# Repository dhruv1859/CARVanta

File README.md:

<h1 align="center">🧬 CARVanta</h1>
<h3 align="center">AI-Augmented CAR-T Cell Target Viability Assessment Platform<br>+ Sentinel HYDRA Bedside Biosensor</h3>

<p align="center">
  <strong>117,000+ lines of code • 778 source files • 214 Python modules • 45 React pages • 50 firmware files • 6-layer medical PCB</strong>
</p>

---

## 🎯 What is CARVanta?

**CARVanta** is a closed-loop immunotherapy intelligence system — an **AI software platform** connected to a **bedside biosensor device** — that turns CAR-T cell therapy target selection from art into science.

> **The core problem:** Selecting the right antigen target is the most critical decision in CAR-T therapy design. A wrong target leads to years of wasted R&D and patient harm. CARVanta automates this decision with data-driven scoring validated against FDA-approved targets, and monitors treatment in real time to catch antigen escape before it kills.

### Key Capabilities

| Module | Description |
|--------|-------------|
| 🔬 **CVS Scoring Engine** | 8-feature adaptive weighted algorithm with multi-source consensus |
| 🤖 **ML Ensemble** | Random Forest + XGBoost classifier + regression ranker |
| 🧠 **LLM Integration** | Grok/Groq/Gemini/OpenAI for dynamic clinical reasoning |
| 🧬 **Genomic Profiler** | Variant calling, HLA typing, TMB calculation, neoantigen prediction |
| 🧑‍⚕️ **Digital Twin** | Patient-specific CRS/ICANS simulation with pharmacokinetic modeling |
| 📊 **Clinical Trials** | Safety monitoring, DSMB reports, RWE analysis, regulatory intelligence |
| 🔍 **NLP Search** | Natural language antigen discovery with semantic intent detection |
| 🏆 **Model Validation** | 5-fold CV, FDA ground-truth validation, ISO/IEC 25010 certification |
| 🌐 **Neural Bridge** | 3D knowledge graph visualization of antigen-disease relationships |
| 💊 **Drug Discovery** | scFv designer, toxicity prediction, CAR construct architecture |
| 📈 **Deep Learning** | Autoencoder anomaly detection, attention mechanisms, neural scoring |
| 🔬 **Sentinel HYDRA** | Real-time 4-channel antigen monitoring with bedside biosensor hardware |

---

## 🏗️ Architecture

```
Patient blood (fingerprick)
        │
        ▼
┌───────────────────────┐
│   SENTINEL HYDRA      │     Bedside device — 100×100mm, ~$79/unit
│   RP2040 + ESP32-S3   │     6-layer medical PCB, ENIG finish
│                       │
│   • 4× potentiostat   │     Sensor data
│   • SpO2 + heart rate │     ─────────────────►
│   • 11-ch spectral    │          WiFi (TLS)
│   • Impedance + temp  │
└───────────┬───────────┘
            │
            ▼
┌─────────────────────────────────────────────────────────────┐
│                    CARVANTA CLOUD PLATFORM                    │
├─────────────────────────────────────────────────────────────┤
│                    Frontend (React + Vite)                    │
│  45 pages • Clinical Precision UI • Glassmorphism Design     │
├─────────────────────────────────────────────────────────────┤
│                    FastAPI Backend (v5)                       │
│  28 routers • Async • CORS • Rate limiting • Audit logging   │
├──────────┬──────────┬──────────┬──────────┬─────────────────┤
│ Scoring  │    ML    │   LLM    │ Genomics │   Validation    │
│ Engine   │ Ensemble │ Insight  │ Pipeline │   & Certify     │
│ (CVS v3) │ (RF+XGB) │(Grok/AI) │(VCF/HLA)│  (ISO 25010)   │
├──────────┴──────────┴──────────┴──────────┴─────────────────┤
│              Data Layer (SQLite / PostgreSQL)                 │
│        biomarker_database.csv • 500+ scored antigens         │
└─────────────────────────────────────────────────────────────┘
            │
            ▼
  Doctor's phone: "CD19 dropping — antigen escape risk. Switch to CD22."
```

> For a deep dive into the full system architecture, see [ARCHITECTURE.md](ARCHITECTURE.md).

---

## 🔬 Sentinel HYDRA — Bedside Biosensor

The **Sentinel HYDRA** is a credit-card-sized medical-grade device that continuously monitors blood biomarkers through a disposable sensor strip. It detects antigen escape — the #1 reason CAR-T fails — in **30 seconds** instead of days via lab tests.

### Hardware Specifications

| Parameter | Value |
|-----------|-------|
| Dimensions | 100mm × 100mm |
| PCB Layers | **6** (signal/ground/analog/power/high-speed/bottom) |
| MCUs | **ESP32-S3** (main) + **RP2040** (sensor coprocessor) |
| Antigen Channels | **4 simultaneous** (CD19, CD22, BCMA, GPRC5D) |
| ADC | ADS1256 — **24-bit**, 8-channel, 30kSPS |
| Potentiostat | 4× LMP91000 (one per antigen channel) |
| SpO2/Heart Rate | MAX30102 integrated sensor |
| Spectral | AS7341 — **11 wavelength channels** |
| Temperature | TMP117 (±0.1°C) + MLX90614 (contactless IR) |
| IMU | LSM6DSO — 6-axis (fall detection) |
| Display | 2.4" IPS TFT (320×240, ST7789) |
| Connectivity | WiFi + BLE (ESP32-S3) |
| Data Logging | microSD + DS3231 RTC |
| Power | USB-C + LiPo battery (BQ24075 charger) |
| Surface Finish | ENIG (immersion gold) — biocompatible |
| Cost per Unit | **~$79** (complete with battery + display + sensor) |

### Manufacturing Files

Production-ready Gerber files for PCB fabrication are available:

📦 **[Sentinel_HYDRA_Gerbers.zip](hardware/sentinel/kicad/Sentinel_HYDRA/Sentinel_HYDRA_Gerbers.zip)** — Upload directly to JLCPCB / PCBWay

Contains:
- 6 copper layers (Digital_Signals, GND_Plane, Analog_Signals, Power_Planes, HighSpeed, Bottom_GND)
- Front/Back solder mask, silkscreen, paste stencil
- Board outline (Edge.Cuts)
- Excellon drill files (PTH + NPTH separated)
- Drill map files
- Gerber job file

> For the full Bill of Materials, see [BOM.md](hardware/sentinel/BOM.md).

---

## 🚀 Quick Start

### Prerequisites

- Python 3.12+
- Node.js 18+
- Git

### 1. Clone & Setup

```bash
git clone https://github.com/dhruv1859/CARVanta.git
cd CARVanta

# Backend
pip install -r requirements.txt
copy .env.example .env
# Edit .env — add your XAI_API_KEY or GROQ_API_KEY for LLM features

# Frontend
cd frontend-react
npm install
```

### 2. Run Locally

```bash
# Terminal 1 — Backend
py -m uvicorn api.main:app --host 0.0.0.0 --port 8001

# Terminal 2 — Frontend
cd frontend-react
npm run dev
```

Open **http://localhost:5173** → full platform is live.

### 3. Train ML Models (Optional)

```bash
py models/train_pipeline.py
```

This runs 5-fold stratified cross-validation and trains the RF+XGBoost ensemble + regression ranker.

### 4. Build Firmware (Optional)

Requires [PlatformIO](https://platformio.org/install):

```bash
# ESP32 main controller
cd hardware/sentinel/firmware/esp32_hydra
pio run

# RP2040 sensor coprocessor
cd hardware/sentinel/firmware/rp2040_hydra
pio run
```

---

## 🧪 Scoring Algorithm

### CVS (CAR-T Viability Score) v3

CARVanta's **original** 8-feature Adaptive Weighted Scoring:

| Feature | Weight | Source |
|---------|--------|--------|
| Tumor Specificity | 25% | TCGA differential expression |
| Safety Score | 20% | GTEx normal tissue risk (inverted) |
| Stability | 12% | Expression consistency |
| Evidence | 10% | Published clinical support |
| Immunogenicity | 10% | Immune recognition potential |
| Surface Accessibility | 8% | UniProt/HPA membrane localization |
| Tissue Risk | 8% | GTEx organ-level heatmap |
| Protein Validation | 7% | HPA protein-level confirmation |

**Adaptive Weight Adjustment:** When real data sources (TCGA, GTEx, HPA) are available, feature weights dynamically shift to give more credence to features backed by real data vs. estimated values.

### ML Ensemble (v4)

The final score blends rule-based CVS with ML predictions:

```
Adaptive Score = (1 - α) × CVS + α × ML_score
```

Where `α` is dynamically adjusted based on data confidence (range: 0.20–0.40).

---

## 🏆 Model Validation & Certification

CARVanta includes a **production-grade validation suite** aligned with ISO/IEC 25010:

| Test | Method | What It Proves |
|------|--------|----------------|
| **Classifier CV** | 5-fold Stratified K-Fold | Accuracy, F1, AUC-ROC, Precision, Recall |
| **Ranker CV** | 5-fold K-Fold Regression | R², MAE, RMSE, Spearman ρ |
| **FDA Ground-Truth** | CD19, BCMA, CD22, GPRC5D | All approved targets must score Tier 1 |
| **Negative Controls** | TP53, RB1, BRCA1, PTEN, APC | Non-viable targets rejected correctly |
| **Robustness** | ±5% feature perturbation | Measures prediction stability |
| **Statistical Significance** | Paired t-test + Wilcoxon | Model vs. 3 random baselines (p < 0.01) |
| **Calibration** | Brier score + log loss | Probability reliability |

Run validation: `GET /api/v5/validation/run`

---

## 🤖 LLM Integration

CARVanta uses LLMs to generate **dynamic clinical reasoning** instead of hardcoded insights:

- **Supported Providers:** Grok (xAI) → Groq → DeepSeek → Gemini → OpenAI
- **Fallback:** If no LLM key is configured, rule-based insights are served
- **Provenance:** Every AI insight displays a badge showing `🤖 LLM Generated` or `📐 Rule-Based`

Set one key in `.env`:
```
XAI_API_KEY=your-grok-key
# or
GROQ_API_KEY=your-groq-key
```

---

## ☁️ Deploy to Railway

### One-Click Deploy

1. Go to [railway.app](https://railway.app) → **New Project** → **Deploy from GitHub repo**
2. Select `dhruv1859/CARVanta`
3. Railway auto-detects `nixpacks.toml` and builds
4. Add environment variables in Railway dashboard:

| Variable | Required | Description |
|----------|----------|-------------|
| `XAI_API_KEY` | ✅ | Grok API key for LLM insights |
| `CARVANTA_ENV` | Optional | Set to `production` |
| `DATABASE_URL` | Optional | PostgreSQL URL (defaults to SQLite) |

5. Railway assigns a public URL → your API is live

### Frontend Deployment

Deploy the React frontend separately on **Vercel** or **Netlify**:

```bash
cd frontend-react
npm run build
# Upload dist/ to Vercel/Netlify
# Set VITE_API_URL to your Railway backend URL
```

---

## 📁 Project Structure

```
CARVanta/
├── api/                        # 28 FastAPI routers (v5)
│   ├── main.py                 # App entrypoint
│   ├── auth.py                 # JWT authentication
│   ├── validation_router.py    # Model validation endpoints
│   └── ...
├── scoring/                    # CVS scoring engine (v3)
├── models/                     # ML pipeline (RF + XGBoost)
├── features/                   # Feature engineering + LLM + FHIR
├── validation/                 # Model validation & certification
├── deep_learning/              # Autoencoder, attention, neural models
├── genomics/                   # Variant calling, HLA, TMB
├── digital_twin/               # Patient simulation engine
├── discovery/                  # Drug discovery, scFv design
├── copilot/                    # Research assistant, RAG engine
├── trials/                     # Clinical trial intelligence
├── frontend-react/             # React 18 + Vite + TypeScript
│   └── src/pages/              # 45 page modules
├── hardware/
│   └── sentinel/
│       ├── kicad/
│       │   └── Sentinel_HYDRA/         # 6-layer KiCad PCB project
│       │       ├── *.kicad_sch         # 7 schematic sheets
│       │       ├── Sentinel_HYDRA.kicad_pcb
│       │       ├── gerbers/            # Production Gerber files
│       │       └── Sentinel_HYDRA_Gerbers.zip
│       ├── firmware/
│       │   ├── esp32_hydra/            # ESP32-S3 firmware (50 files)
│       │   └── rp2040_hydra/           # RP2040 firmware
│       ├── BOM.md                      # Bill of materials (~$79/unit)
│       └── README.md                   # Hardware documentation
├── data/                       # Biomarker database + reports
├── ARCHITECTURE.md             # Full system architecture
├── nixpacks.toml               # Railway deployment config
├── railway.json                # Railway service config
└── requirements.txt            # Python dependencies
```

---

## 🔑 API Endpoints

### Core Scoring
| Endpoint | Method | Description |
|----------|--------|-------------|
| `/api/v5/score` | POST | Score a single antigen |
| `/api/v5/batch_score` | POST | Score multiple antigens |
| `/api/v5/rankings` | GET | Global antigen leaderboard |
| `/api/v5/nlp/query` | POST | Natural language search |

### Validation
| Endpoint | Method | Description |
|----------|--------|-------------|
| `/api/v5/validation/run` | GET | Full validation suite |
| `/api/v5/validation/quick` | GET | Quick classifier + FDA check |
| `/api/v5/validation/fda-targets` | GET | FDA ground-truth only |
| `/api/v5/validation/certification` | GET | ISO/IEC 25010 report |

### Clinical
| Endpoint | Method | Description |
|----------|--------|-------------|
| `/api/v5/digital-twin/simulate` | POST | Patient simulation |
| `/api/v5/trials/clinical-trials` | GET | Trial lookup by antigen |
| `/api/v5/genomics/analyze-variants` | POST | Genomic variant analysis |

Full API docs: `http://localhost:8001/docs` (Swagger UI)

---

## 🛡️ Security & Compliance

- **ISO/IEC 25010** aligned model validation and certification
- **FDA 21 CFR Part 11** concepts for electronic records
- **GAMP 5** risk-based approach compliance framework
- **LLM Provenance** — all AI outputs labeled with origin (LLM vs Rule-Based)
- **Audit Logging** — all scoring requests logged with timestamps
- **CORS + Rate Limiting** middleware (configurable)

See [security.md](security.md) for vulnerability reporting and [PRIVACY_POLICY.md](PRIVACY_POLICY.md) for HIPAA alignment.

---

## 📄 Documentation

| Document | Description |
|----------|-------------|
| [ARCHITECTURE.md](ARCHITECTURE.md) | Full system architecture (software + hardware + firmware) |
| [BOM.md](hardware/sentinel/BOM.md) | Sentinel HYDRA bill of materials |
| [ROADMAP.md](ROADMAP.md) | Product roadmap and future plans |
| [MODULES.md](MODULES.md) | Module registry and build order |
| [CHANGELOG.md](CHANGELOG.md) | Version history |
| [contributing.md](contributing.md) | Contribution guidelines |
| [security.md](security.md) | Security policy |
| [CODE_OF_CONDUCT.md](CODE_OF_CONDUCT.md) | Community code of conduct |
| [MODEL_CARD.md](MODEL_CARD.md) | ML model documentation |
| [ISO_13485_ALIGNMENT.md](ISO_13485_ALIGNMENT.md) | Quality management alignment |
| [PRIVACY_POLICY.md](PRIVACY_POLICY.md) | HIPAA compliance disclosure |

---

## 📄 License

Business Source License 1.1 (BUSL-1.1). See [LICENSE](LICENSE) for details.

---

## 👨‍💻 Author

**Dhruv** — [@dhruv1859](https://github.com/dhruv1859)

---

<p align="center">
  <strong>CARVanta</strong> — Turning immunotherapy target selection from art into science.
</p>

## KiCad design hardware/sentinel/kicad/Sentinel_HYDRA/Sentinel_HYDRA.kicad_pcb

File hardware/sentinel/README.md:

# CARVanta Sentinel v2.0 — 6-Layer Medical-Grade PCB
## Multi-Channel Antigen Escape Detection System

### Why 6 Layers?

This board monitors **4 antigens simultaneously** (CD19, CD22, BCMA, GPRC5D),
meaning 4 independent electrochemical channels that MUST be electrically isolated
from each other and from the digital noise of the ESP32 + WiFi radio.

A 2-layer board cannot achieve this. Here's why each layer exists:

```
Layer 1 (F.Cu)  — Digital signals: SPI, I2C, UART, USB, GPIO
Layer 2 (GND)   — Continuous ground plane (EMI shield between digital & analog)
Layer 3 (INNER1)— Analog signals: 4× potentiostat outputs, ADC inputs, sensor traces
Layer 4 (PWR)   — Power planes: 3.3V_DIGITAL, 3.3V_ANALOG, 1.8V_CORE, VBAT
Layer 5 (INNER2)— High-speed: USB 2.0 differential pair, WiFi RF routing
Layer 6 (B.Cu)  — Component pads, ground pour, thermal relief
```

### Board Specifications

| Parameter | v1.0 (old) | v2.0 (new) |
|-----------|-----------|-----------|
| Dimensions | 80×55mm | 95×65mm |
| Layers | 2 | **6** |
| Channels | 1 antigen | **4 simultaneous** |
| ADC | 1× ADS1115 (16-bit) | **1× ADS1256 (24-bit, 8ch)** |
| Potentiostat | 1× LMP91000 | **4× LMP91000** |
| Power domains | 1 (3.3V) | **4 (3.3V_D, 3.3V_A, 1.8V, VBAT)** |
| Analog isolation | None | **Split ground plane + ferrite bead** |
| Data logging | None | **microSD + RTC** |
| Patient vitals | None | **MAX30102 SpO2/HR + MLX90614 temp** |
| Impedance control | No | **90Ω USB, 50Ω RF** |
| ESD protection | No | **TVS diodes on all I/O** |
| Cost per unit | $17 | **~$45-55** |

### Stackup (6-Layer, 1.6mm FR4)

```
┌─────────────────────────────────────────────────────────┐
│ Layer 1: F.Cu (Signal - Digital)          35µm copper   │
│   └─ SPI bus, I2C bus, UART, GPIO, LED data            │
├─────────────────────────────────────────────────────────┤
│ Prepreg: 0.2mm FR4 (εr=4.5)                            │
├─────────────────────────────────────────────────────────┤
│ Layer 2: GND (Solid Ground Plane)         35µm copper   │
│   └─ Continuous pour, NO cuts, NO traces                │
│   └─ Acts as EMI shield between digital L1 & analog L3 │
├─────────────────────────────────────────────────────────┤
│ Core: 0.36mm FR4                                        │
├─────────────────────────────────────────────────────────┤
│ Layer 3: INNER1 (Signal - Analog)         35µm copper   │
│   └─ 4× LMP91000 VOUT traces (guarded)                 │
│   └─ ADS1256 analog inputs (star routing)               │
│   └─ Sensor connector traces (kelvin connection)        │
├─────────────────────────────────────────────────────────┤
│ Prepreg: 0.2mm FR4                                      │
├─────────────────────────────────────────────────────────┤
│ Layer 4: PWR (Power Planes)               35µm copper   │
│   └─ Zone 1: 3.3V_DIGITAL (ESP32, TFT, LEDs)          │
│   └─ Zone 2: 3.3V_ANALOG (LMP91000s, ADS1256)         │
│   └─ Zone 3: VBAT (battery direct)                      │
│   └─ Zone 4: 1.8V (ESP32 core, if needed)              │
├─────────────────────────────────────────────────────────┤
│ Core: 0.36mm FR4                                        │
├─────────────────────────────────────────────────────────┤
│ Layer 5: INNER2 (High-Speed Signals)      35µm copper   │
│   └─ USB D+/D- differential pair (90Ω impedance)       │
│   └─ ESP32 antenna feed (50Ω microstrip)                │
│   └─ SD card high-speed data lines                      │
├─────────────────────────────────────────────────────────┤
│ Prepreg: 0.2mm FR4                                      │
├─────────────────────────────────────────────────────────┤
│ Layer 6: B.Cu (Signal + Ground Pour)      35µm copper   │
│   └─ Component pads (bottom-side ICs)                   │
│   └─ Ground pour for thermal dissipation                │
│   └─ Mounting hole connections                          │
└─────────────────────────────────────────────────────────┘
Total thickness: ~1.6mm
```

### Design Rules (Medical Grade)

| Rule | Value | Reason |
|------|-------|--------|
| Min trace width | 0.15mm (6mil) | JLCPCB 6-layer capability |
| Min clearance | 0.15mm | IPC-2221 Class 2 |
| USB diff pair | 0.18mm trace, 0.15mm gap | 90Ω impedance on L5 |
| Analog traces | 0.25mm, guarded | Noise rejection |
| Power traces | 0.5mm minimum | Current handling |
| Via size | 0.3mm drill, 0.6mm pad | Standard via |
| Via-in-pad | Allowed (filled & capped) | For QFN packages |
| Copper weight | 1oz (35µm) all layers | Standard |
| Surface finish | ENIG (gold) | Corrosion resistance, biocompat |
| Solder mask | Matte black | Premium aesthetic |
| Silkscreen | White, both sides | Component labels |

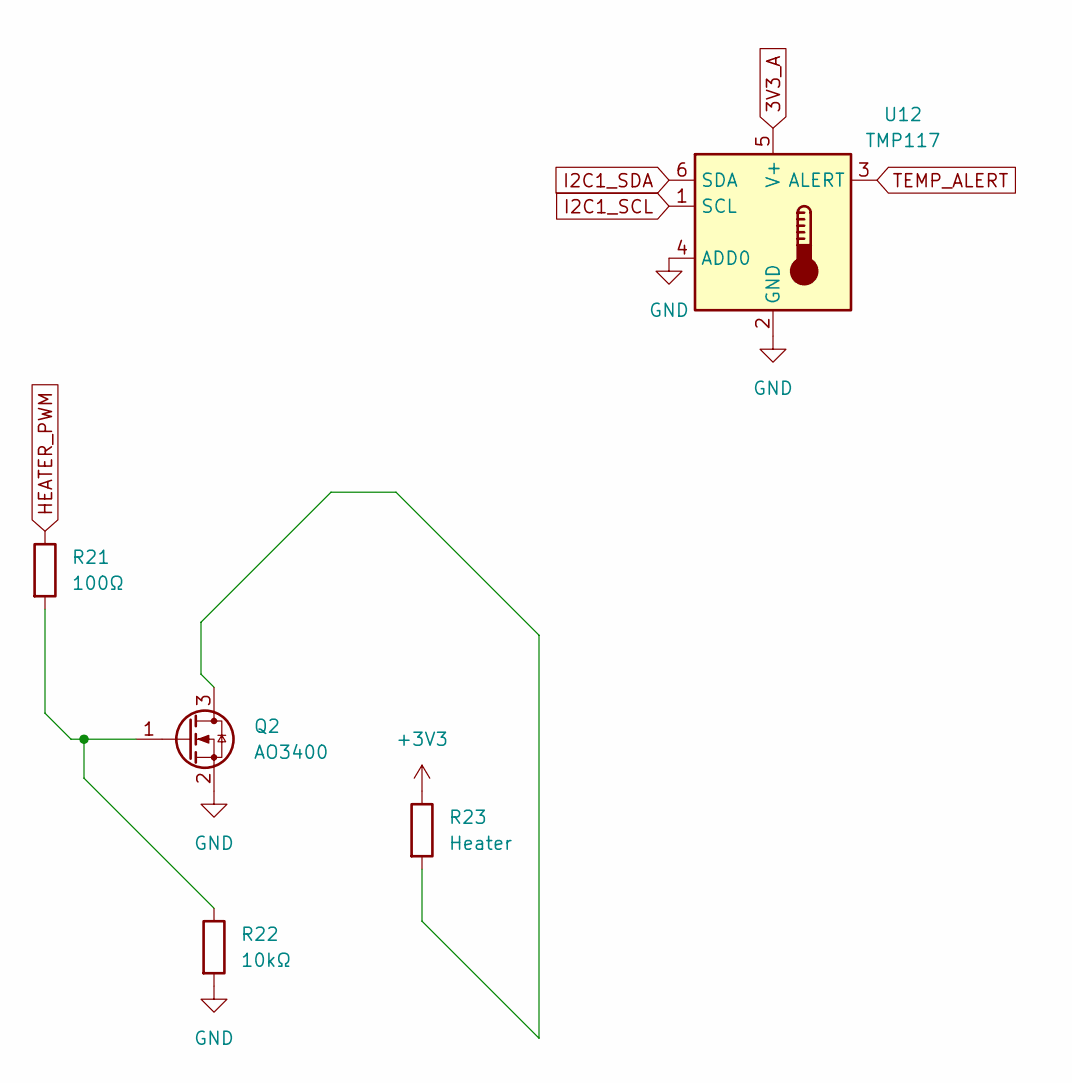
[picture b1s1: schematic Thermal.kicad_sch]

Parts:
Q2: AO3400; SOT-23
R21: 100Ω; R_0402_1005Metric
R22: 10kΩ; R_0402_1005Metric
R23: Heater
U12: TMP117; WSON-6-1EP_2x2mm_P0.65mm_EP1x1.6mm

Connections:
3V3_A: U12.5 (V+); also elsewhere on the board
+3V3: Q2.2 (S), Q2.3 (D), R22.2, R23.2, U12.2 (GND), U12.4 (ADD0); also elsewhere on the board
HEATER_PWM: R21.1; also elsewhere on the board
I2C1_SCL: U12.1 (SCL); also elsewhere on the board
I2C1_SDA: U12.6 (SDA); also elsewhere on the board
unnamed: Q2.1 (G), R21.2, R22.1
TEMP_ALERT: U12.3 (ALERT)

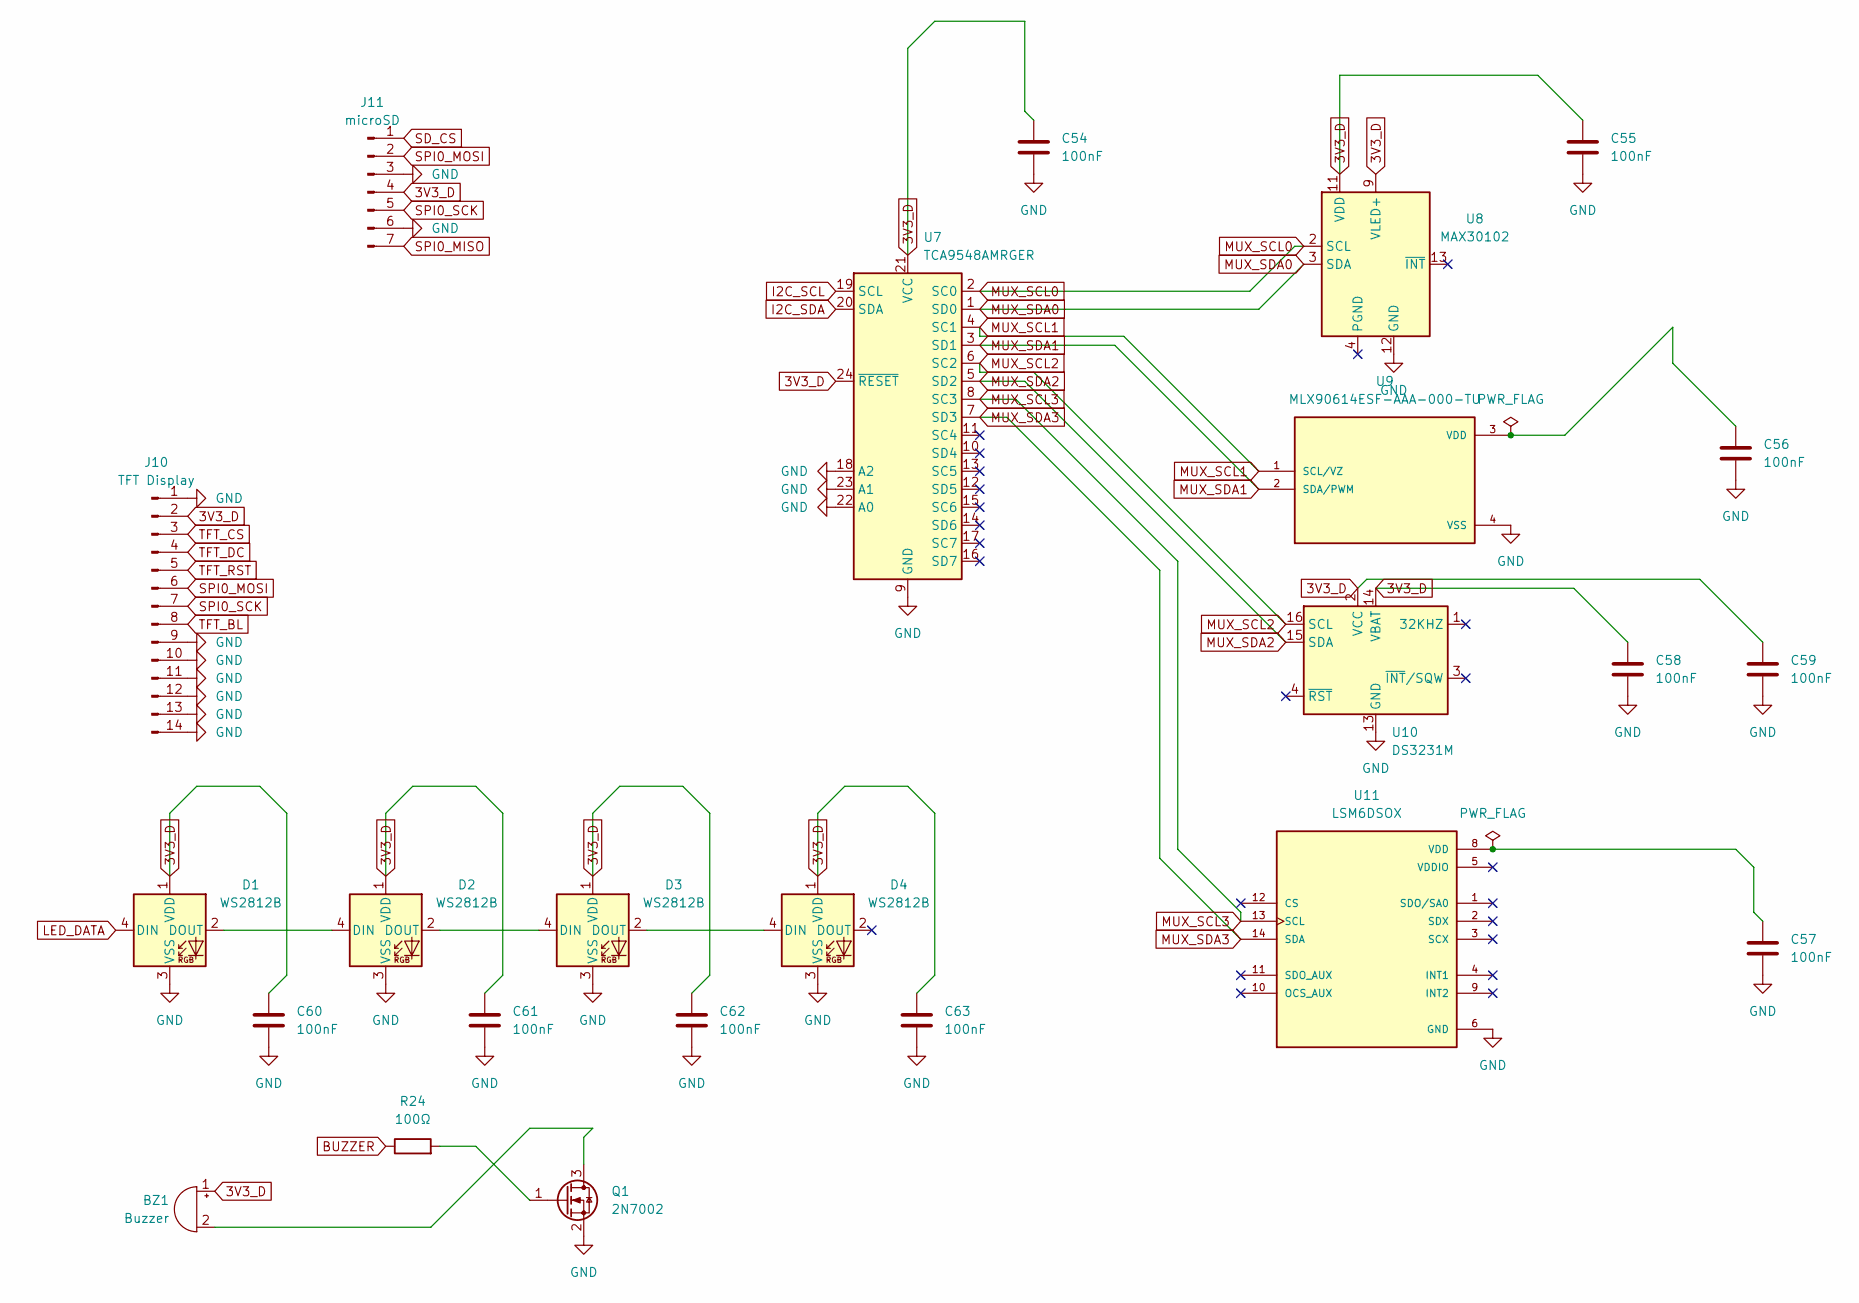
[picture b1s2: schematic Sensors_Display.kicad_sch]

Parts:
BZ1: Buzzer; Buzzer_12x9.5RM7.6
C54, C55, C56, C57, C58, C59, C60, C61, C62, C63: 100nF; C_0402_1005Metric
D1, D2, D3, D4: WS2812B; LED_WS2812B_PLCC4_5.0x5.0mm_P3.2mm
J10: TFT Display; Hirose_FH12-14S-0.5SH_1x14-1MP_P0.50mm_Horizontal
J11: microSD; microSD_HC_Molex_104031-0811
Q1: 2N7002; SOT-23
R24: 100Ω; R_0402_1005Metric
U7: TCA9548AMRGER; Texas_RGE0024C_VQFN-24-1EP_4x4mm_P0.5mm_EP2.1x2.1mm
U8: MAX30102; Maxim_OLGA-14_3.3x5.6mm_P0.8mm
U9: MLX90614ESF-AAA-000-TU; TO254P912H435-4; PARTREV 13
U10: DS3231M; SOIC-16W_7.5x10.3mm_P1.27mm
U11: LSM6DSOX; PQFN50P250X300X86-14N; PARTREV 3.0

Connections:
3V3_D: BZ1.1 (+), C54.1, C55.1, C58.1, C59.1, C60.1, C61.1, C62.1, C63.1, D1.1 (VDD), D2.1 (VDD), D3.1 (VDD), D4.1 (VDD), J10.2, J11.4, U7.21 (VCC), U7.24 (~RESET), U8.9 (VLED+), U8.10 (VLED+), U8.11 (VDD), U10.2 (VCC), U10.14 (VBAT); also elsewhere on the board
+3V3: C54.2, C55.2, C56.2, C57.2, C58.2, C59.2, C60.2, C61.2, C62.2, C63.2, D1.3 (VSS), D2.3 (VSS), D3.3 (VSS), D4.3 (VSS), J10.1, J10.9, J10.10, J10.11, J10.12, J10.13, J10.14, J11.3, J11.6, Q1.2 (S), U7.9 (GND), U7.18 (A2), U7.22 (A0), U7.23 (A1), U8.12 (GND), U9.4 (VSS), U10.5 (GND), U10.6 (GND), U10.7 (GND), U10.8 (GND), U10.9 (GND), U10.10 (GND), U10.11 (GND), U10.12 (GND), U10.13 (GND), U11.6 (GND), U11.7 (GND); also elsewhere on the board
BUZZER: R24.1; also elsewhere on the board
I2C_SCL: U7.19 (SCL); also elsewhere on the board
I2C_SDA: U7.20 (SDA); also elsewhere on the board
LED_DATA: D1.4 (DIN); also elsewhere on the board
MUX_SCL0: U7.2 (SC0), U8.2 (SCL)
MUX_SCL1: U7.4 (SC1), U9.1 (SCL/VZ)
MUX_SCL2: U7.6 (SC2), U10.16 (SCL)
MUX_SCL3: U7.8 (SC3), U11.13 (SCL)
MUX_SDA0: U7.1 (SD0), U8.3 (SDA)
MUX_SDA1: U7.3 (SD1), U9.2 (SDA/PWM)
MUX_SDA2: U7.5 (SD2), U10.15 (SDA)
MUX_SDA3: U7.7 (SD3), U11.14 (SDA)
unnamed: BZ1.2 (-), Q1.3 (D)
unnamed: D1.2 (DOUT), D2.4 (DIN)
unnamed: D2.2 (DOUT), D3.4 (DIN)
unnamed: D3.2 (DOUT), D4.4 (DIN)
unnamed: Q1.1 (G), R24.2
unnamed: C56.1, U9.3 (VDD)
unnamed: C57.1, U11.8 (VDD)
SD_CS: J11.1; also elsewhere on the board
SPI0_MISO: J11.7; also elsewhere on the board
SPI0_MOSI: J10.6, J11.2; also elsewhere on the board
SPI0_SCK: J10.7, J11.5; also elsewhere on the board
TFT_BL: J10.8; also elsewhere on the board
TFT_CS: J10.3; also elsewhere on the board
TFT_DC: J10.4; also elsewhere on the board
TFT_RST: J10.5; also elsewhere on the board

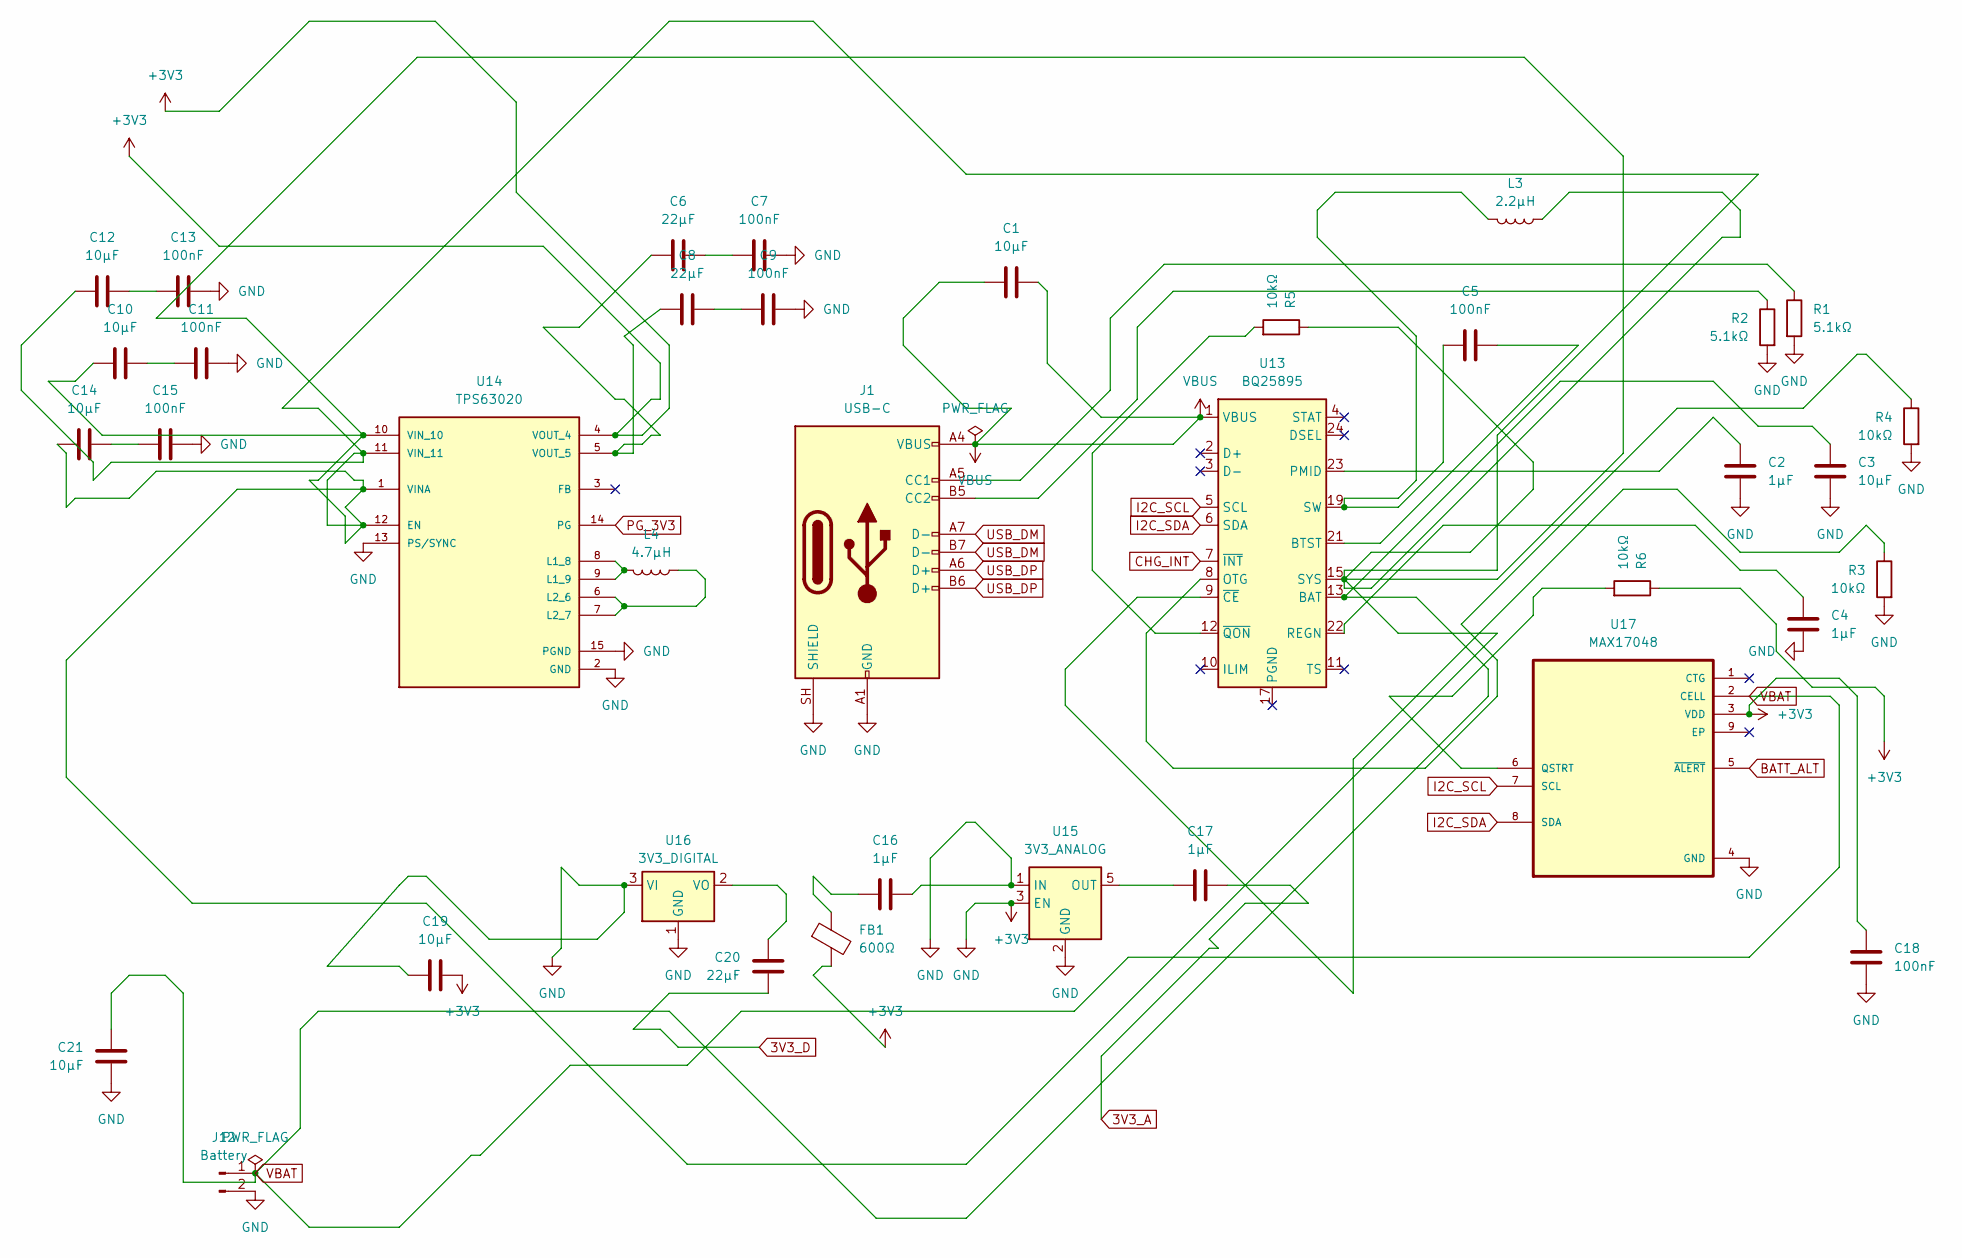
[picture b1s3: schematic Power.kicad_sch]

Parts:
C1, C3, C10, C12, C14, C19, C21: 10µF; C_0805_2012Metric
C2, C4, C16, C17: 1µF; C_0402_1005Metric
C5, C7, C9, C11, C13, C15, C18: 100nF; C_0402_1005Metric
C6, C8, C20: 22µF; C_0805_2012Metric
FB1: 600Ω; L_0402_1005Metric
J1: USB-C; USB_C_Receptacle_HRO_TYPE-C-31-M-12
J12: Battery; JST_PH_B2B-PH-K_1x02_P2.00mm_Vertical
L3: 2.2µH; L_Taiyo-Yuden_NR-40xx
L4: 4.7µH; L_Taiyo-Yuden_NR-40xx
R1, R2: 5.1kΩ; R_0402_1005Metric
R3, R4, R5, R6: 10kΩ; R_0402_1005Metric
U13: BQ25895; Texas_RTW_WQFN-24-1EP_4x4mm_P0.5mm_EP2.7x2.7mm_ThermalVias
U14: TPS63020; IC_TPS63020DSJR
U15: 3V3_ANALOG; SOT-23-5
U16: 3V3_DIGITAL; SOT-223-3_TabPin2
U17: MAX17048; SON50P200X200X80-9N

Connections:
3V3_A: C17.1; also elsewhere on the board
3V3_D: C20.2; also elsewhere on the board
+3V3: C2.1, C3.1, C4.1, C7.1, C9.1, C11.1, C13.1, C15.1, C16.1, C18.1, C18.2, C19.1, C19.2, C21.2, FB1.2, J1.A1 (GND), J1.A12 (GND), J1.B1 (GND), J1.B12 (GND), J1.SH (SHIELD), J12.2, R1.2, R2.2, R3.2, R4.2, R6.1, U14.2 (GND), U14.4 (VOUT_4), U14.13 (PS/SYNC), U14.15 (PGND), U15.1 (IN), U15.2 (GND), U15.3 (EN), U16.1 (GND), U16.3 (VI), U17.3 (VDD), U17.4 (GND); also elsewhere on the board
BATT_ALT: U17.5 (~ALERT); also elsewhere on the board
CHG_INT: U13.7 (~INT); also elsewhere on the board
I2C_SCL: U13.5 (SCL), U17.7 (SCL); also elsewhere on the board
I2C_SDA: U13.6 (SDA), U17.8 (SDA); also elsewhere on the board
unnamed: C5.1, L3.2, U13.19 (SW), U13.20 (SW)
unnamed: C6.1, C7.2
unnamed: C8.1, C9.2
unnamed: C10.1, C11.2
unnamed: C12.1, C13.2
unnamed: C14.1, C15.2
unnamed: C16.2, FB1.1
unnamed: J1.A5 (CC1), R1.1
unnamed: J1.B5 (CC2), R2.1
unnamed: C5.2, U13.21 (BTST)
unnamed: R4.1, U13.8 (OTG)
unnamed: C2.2, U13.23 (PMID)
unnamed: C4.2, U13.22 (REGN)
unnamed: R3.1, U13.9 (~CE)
unnamed: R5.2, U13.12 (~QON)
unnamed: C10.2, C12.2, C14.2, L3.1, R5.1, U13.15 (SYS), U13.16 (SYS), U14.1 (VINA), U14.10 (VIN_10), U14.11 (VIN_11), U14.12 (EN)
unnamed: L4.2, U14.8 (L1_8), U14.9 (L1_9)
unnamed: C6.2, C8.2, U14.5 (VOUT_5)
unnamed: C17.2, U15.5 (OUT)
unnamed: C20.1, U16.2 (VO)
unnamed: R6.2, U17.6 (QSTRT)
PG_3V3: U14.14 (PG); also elsewhere on the board
USB_DM: J1.A7 (D-), J1.B7 (D-); also elsewhere on the board
USB_DP: J1.A6 (D+), J1.B6 (D+); also elsewhere on the board
VBAT: C3.2, C21.1, J12.1, U13.13 (BAT), U13.14 (BAT), U17.2 (CELL)
VBUS: C1.1, C1.2, J1.A4 (VBUS), J1.A9 (VBUS), J1.B4 (VBUS), J1.B9 (VBUS), U13.1 (VBUS)

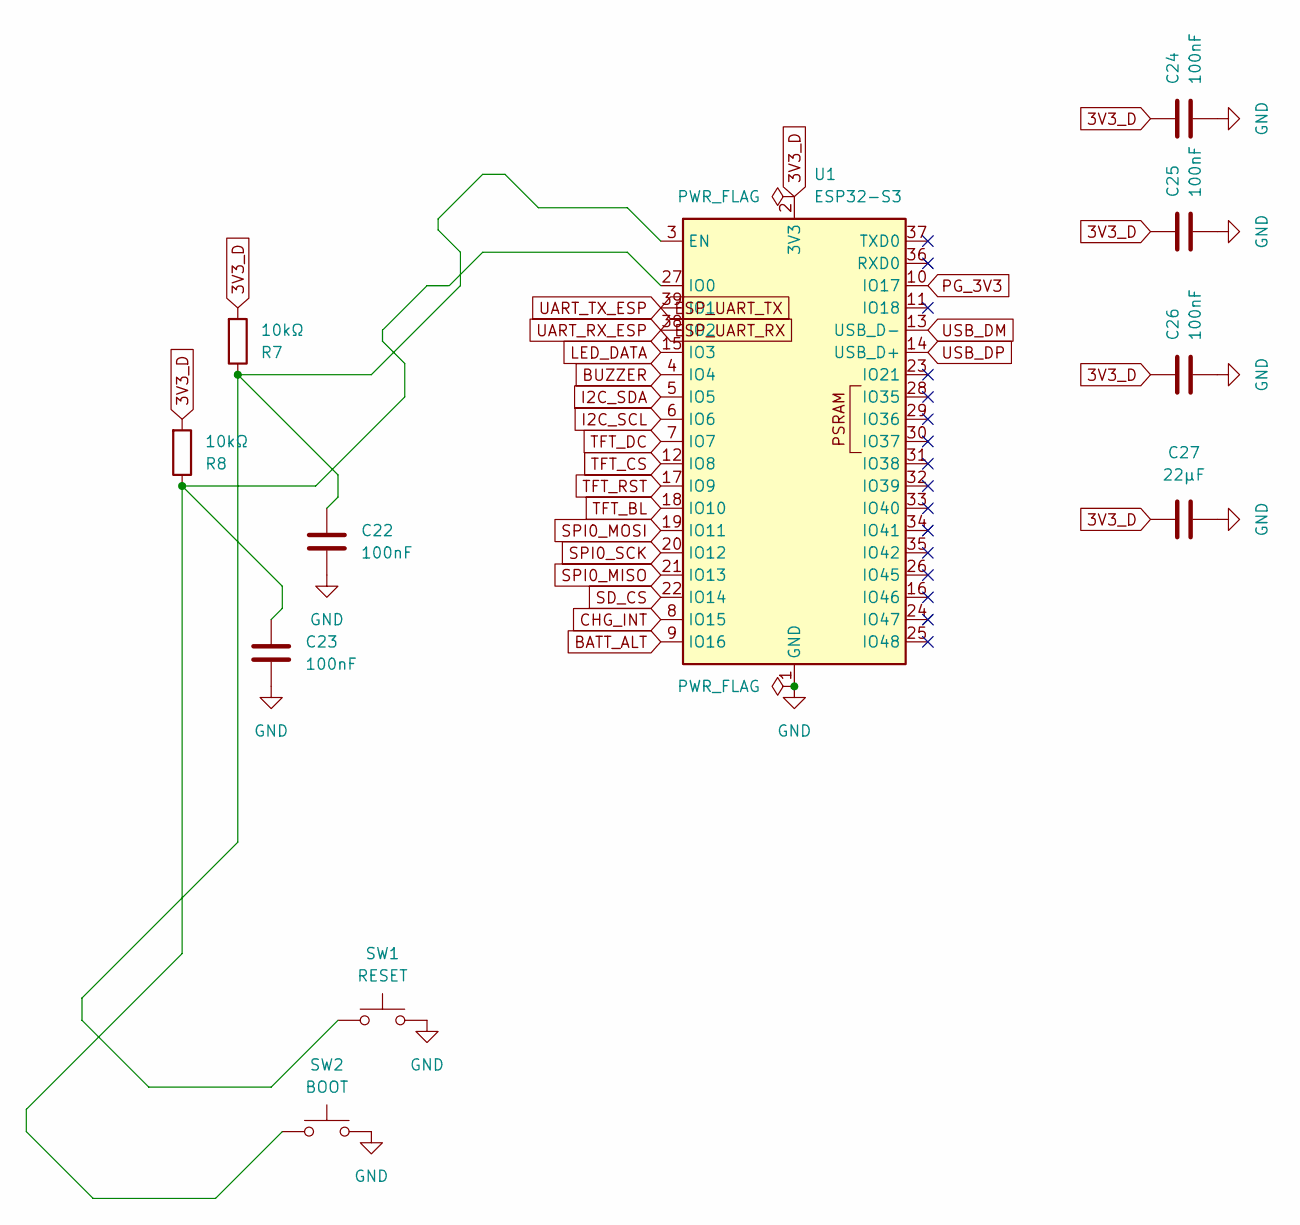
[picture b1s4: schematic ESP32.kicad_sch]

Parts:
C22, C23, C24, C25, C26: 100nF; C_0402_1005Metric
C27: 22µF; C_0805_2012Metric
R7, R8: 10kΩ; R_0402_1005Metric
SW1: RESET; SW_SPST_TL3342
SW2: BOOT; SW_SPST_TL3342
U1: ESP32-S3; ESP32-S3-WROOM-1

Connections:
3V3_D: C24.1, C25.1, C26.1, C27.1, R7.2, R8.2, U1.2 (3V3); also elsewhere on the board
+3V3: C22.2, C23.2, C24.2, C25.2, C26.2, C27.2, SW1.2, SW2.2, U1.1 (GND), U1.40 (GND), U1.41 (GND); also elsewhere on the board
BATT_ALT: U1.9 (IO16); also elsewhere on the board
BUZZER: U1.4 (IO4); also elsewhere on the board
CHG_INT: U1.8 (IO15); also elsewhere on the board
ESP_UART_RX: U1.38 (IO2); also elsewhere on the board
ESP_UART_TX: U1.39 (IO1); also elsewhere on the board
I2C_SCL: U1.6 (IO6); also elsewhere on the board
I2C_SDA: U1.5 (IO5); also elsewhere on the board
LED_DATA: U1.15 (IO3); also elsewhere on the board
unnamed: C22.1, R7.1, SW1.1, U1.3 (EN)
unnamed: C23.1, R8.1, SW2.1, U1.27 (IO0)
PG_3V3: U1.10 (IO17); also elsewhere on the board
SD_CS: U1.22 (IO14); also elsewhere on the board
SPI0_MISO: U1.21 (IO13); also elsewhere on the board
SPI0_MOSI: U1.19 (IO11); also elsewhere on the board
SPI0_SCK: U1.20 (IO12); also elsewhere on the board
TFT_BL: U1.18 (IO10); also elsewhere on the board
TFT_CS: U1.12 (IO8); also elsewhere on the board
TFT_DC: U1.7 (IO7); also elsewhere on the board
TFT_RST: U1.17 (IO9); also elsewhere on the board
USB_DM: U1.13 (USB_D-); also elsewhere on the board
USB_DP: U1.14 (USB_D+); also elsewhere on the board

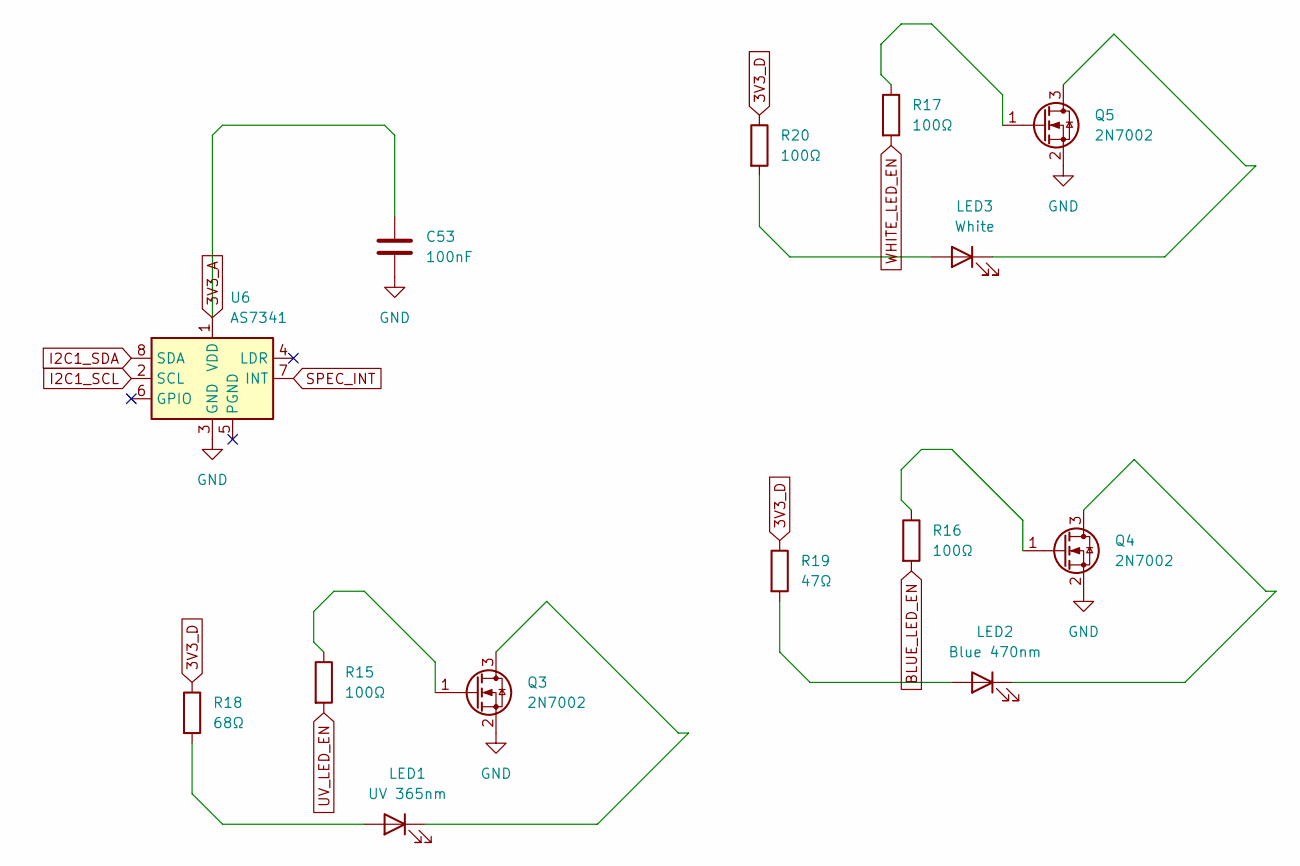
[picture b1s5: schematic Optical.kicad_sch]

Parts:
C53: 100nF; C_0402_1005Metric
LED1: UV 365nm; LED_0805_2012Metric
LED2: Blue 470nm; LED_0805_2012Metric
LED3: White; LED_0805_2012Metric
Q3, Q4, Q5: 2N7002; SOT-23
R15, R16, R17, R20: 100Ω; R_0402_1005Metric
R18: 68Ω; R_0402_1005Metric
R19: 47Ω; R_0402_1005Metric
U6: AS7341; AMS_OLGA-8_2x3.1mm_P0.8mm

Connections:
3V3_A: C53.1, U6.1 (VDD); also elsewhere on the board
3V3_D: R18.1, R19.1, R20.1; also elsewhere on the board
+3V3: C53.2, Q3.2 (S), Q4.2 (S), Q5.2 (S), U6.3 (GND); also elsewhere on the board
BLUE_LED_EN: R16.2; also elsewhere on the board
I2C1_SCL: U6.2 (SCL); also elsewhere on the board
I2C1_SDA: U6.8 (SDA); also elsewhere on the board
unnamed: LED1.2 (A), R18.2
unnamed: LED1.1 (K), Q3.3 (D)
unnamed: LED2.2 (A), R19.2
unnamed: LED2.1 (K), Q4.3 (D)
unnamed: LED3.2 (A), R20.2
unnamed: LED3.1 (K), Q5.3 (D)
unnamed: Q3.1 (G), R15.1
unnamed: Q4.1 (G), R16.1
unnamed: Q5.1 (G), R17.1
SPEC_INT: U6.7 (INT); also elsewhere on the board
UV_LED_EN: R15.2; also elsewhere on the board
WHITE_LED_EN: R17.2; also elsewhere on the board

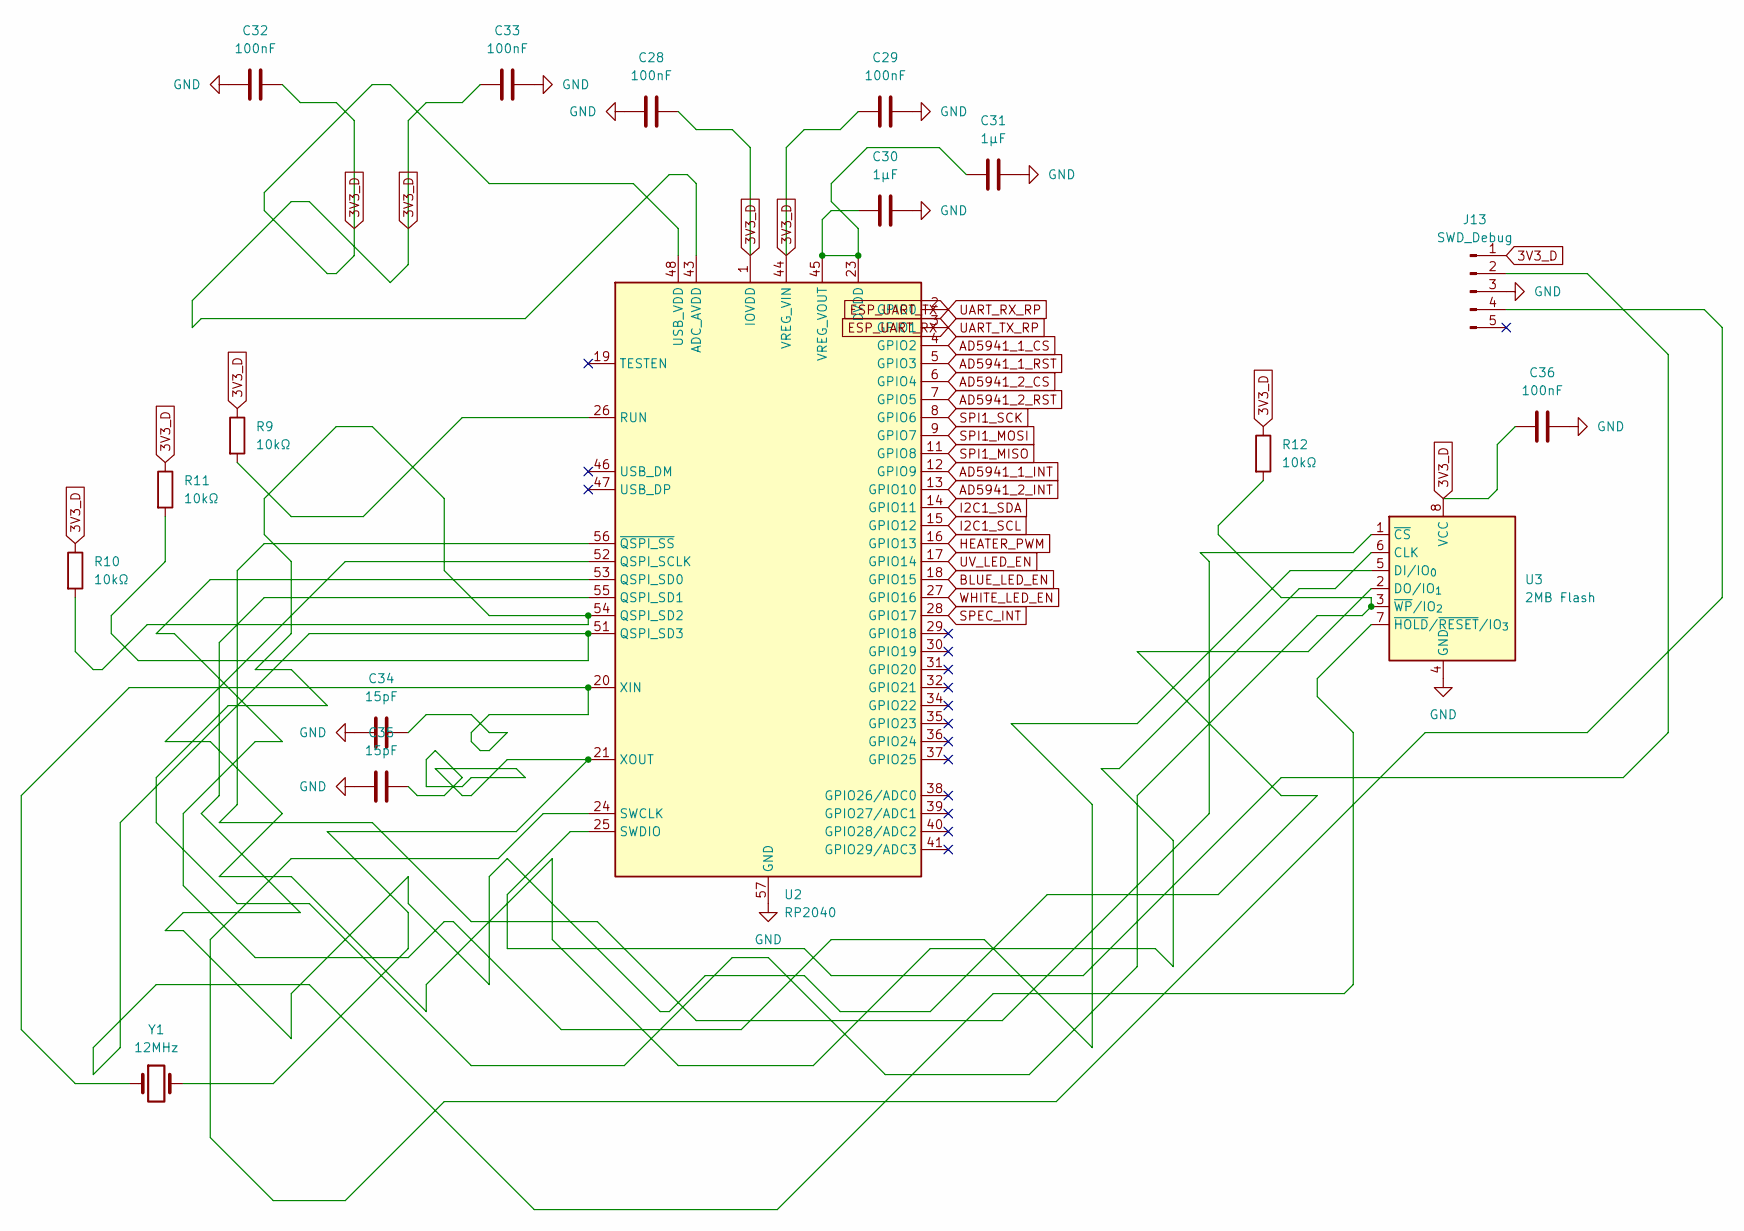
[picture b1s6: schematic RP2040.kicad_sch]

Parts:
C28, C29, C32, C33, C36: 100nF; C_0402_1005Metric
C30, C31: 1µF; C_0402_1005Metric
C34, C35: 15pF; C_0402_1005Metric
J13: SWD_Debug; Tag-Connect_TC2050-IDC-FP_2x05_P1.27mm_Vertical
R9, R10, R11, R12: 10kΩ; R_0402_1005Metric
U2: RP2040; QFN-56-1EP_7x7mm_P0.4mm_EP3.2x3.2mm
U3: 2MB Flash; SOIC-8_3.9x4.9mm_P1.27mm
Y1: 12MHz; Crystal_SMD_3215-2Pin_3.2x1.5mm

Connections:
3V3_D: C28.1, C29.1, C32.1, C33.1, C36.1, J13.1, R9.1, R10.1, R11.1, R12.1, U2.1 (IOVDD), U2.10 (IOVDD), U2.22 (IOVDD), U2.33 (IOVDD), U2.42 (IOVDD), U2.43 (ADC_AVDD), U2.44 (VREG_VIN), U2.48 (USB_VDD), U2.49 (IOVDD), U3.8 (VCC); also elsewhere on the board
+3V3: C28.2, C29.2, C30.2, C31.2, C32.2, C33.2, C34.2, C35.2, C36.2, J13.3, U2.57 (GND), U3.4 (GND); also elsewhere on the board
AD5941_1_CS: U2.4 (GPIO2); also elsewhere on the board
AD5941_1_INT: U2.12 (GPIO9); also elsewhere on the board
AD5941_1_RST: U2.5 (GPIO3); also elsewhere on the board
AD5941_2_CS: U2.6 (GPIO4); also elsewhere on the board
AD5941_2_INT: U2.13 (GPIO10); also elsewhere on the board
AD5941_2_RST: U2.7 (GPIO5); also elsewhere on the board
BLUE_LED_EN: U2.18 (GPIO15); also elsewhere on the board
ESP_UART_RX: U2.3 (GPIO1); also elsewhere on the board
ESP_UART_TX: U2.2 (GPIO0); also elsewhere on the board
HEATER_PWM: U2.16 (GPIO13); also elsewhere on the board
I2C1_SCL: U2.15 (GPIO12); also elsewhere on the board
I2C1_SDA: U2.14 (GPIO11); also elsewhere on the board
unnamed: J13.2, U2.25 (SWDIO)
unnamed: J13.4, U2.24 (SWCLK)
unnamed: U2.52 (QSPI_SCLK), U3.6 (CLK)
unnamed: U2.53 (QSPI_SD0), U3.5 (DI/IO_{0})
unnamed: U2.55 (QSPI_SD1), U3.2 (DO/IO_{1})
unnamed: R10.2, R12.2, U2.54 (QSPI_SD2), U3.3 (~WP/IO_{2})
unnamed: R11.2, U2.51 (QSPI_SD3), U3.7 (~HOLD/~RESET/IO_{3})
unnamed: R9.2, U2.26 (RUN)
unnamed: C30.1, C31.1, U2.23 (DVDD), U2.45 (VREG_VOUT), U2.50 (DVDD)
unnamed: C34.1, U2.20 (XIN), Y1.1
unnamed: C35.1, U2.21 (XOUT), Y1.2
unnamed: U2.56 (~QSPI_SS), U3.1 (~CS)
SPEC_INT: U2.28 (GPIO17); also elsewhere on the board
SPI1_MISO: U2.11 (GPIO8); also elsewhere on the board
SPI1_MOSI: U2.9 (GPIO7); also elsewhere on the board
SPI1_SCK: U2.8 (GPIO6); also elsewhere on the board
UV_LED_EN: U2.17 (GPIO14); also elsewhere on the board
WHITE_LED_EN: U2.27 (GPIO16); also elsewhere on the board

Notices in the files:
README.md:
License: BUSL-1.1
